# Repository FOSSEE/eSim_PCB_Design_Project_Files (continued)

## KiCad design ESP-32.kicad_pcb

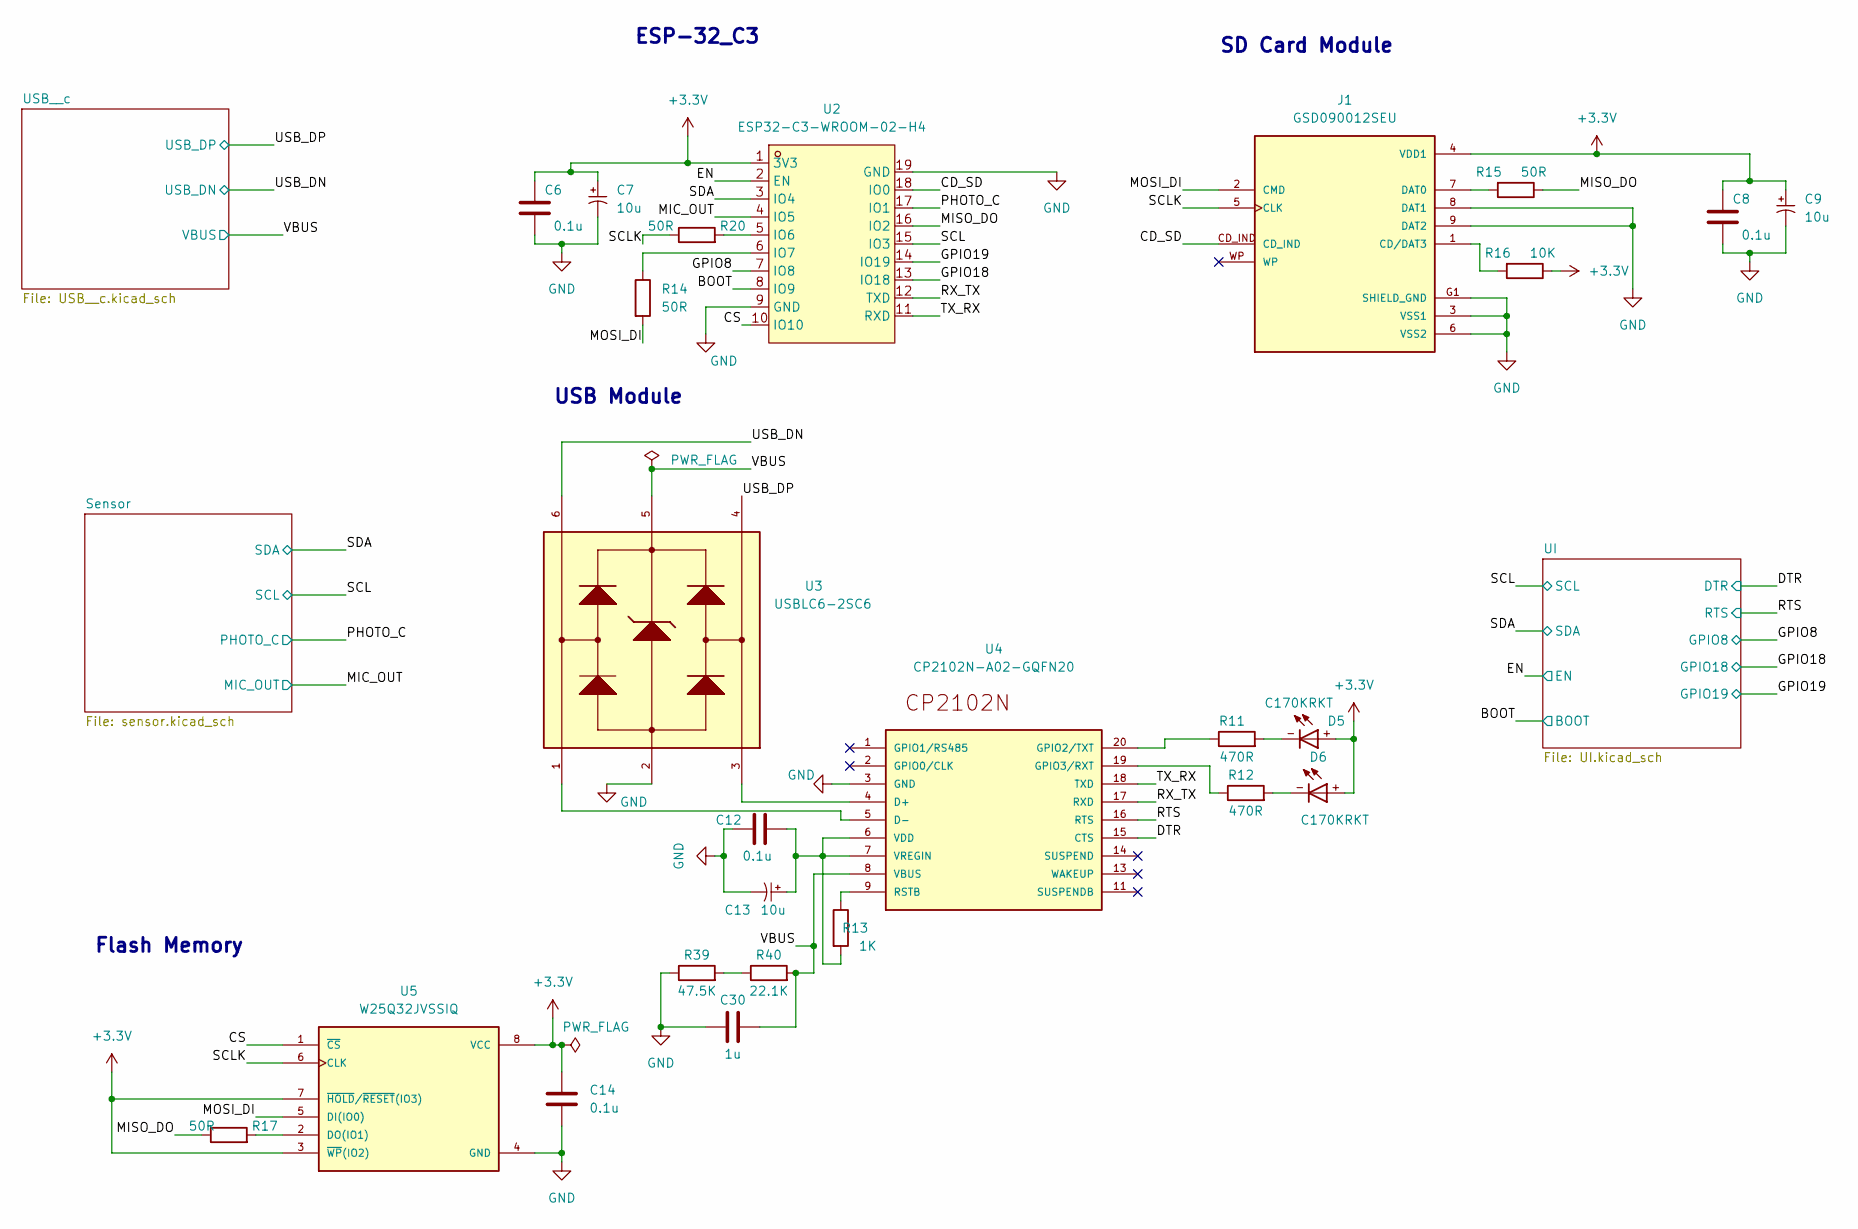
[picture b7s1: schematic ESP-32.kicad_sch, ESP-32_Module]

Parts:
C6, C8, C12, C14: 0.1u; C_0805_2012Metric
C7, C9, C13: 10u; C_0805_2012Metric
C30: 1u; C_0805_2012Metric
D5, D6: C170KRKT; DIOC200X125X110; MPN LTST-C170KRKT
J1: GSD090012SEU; AMPHENOL_GSD090012SEU; MPN GSD090012SEU
R11, R12: 470R; R_0805_2012Metric
R13: 1K; R_0805_2012Metric
R14, R15, R17, R20: 50R; R_0805_2012Metric
R16: 10K; R_0805_2012Metric
R39: 47.5K; R_0805_2012Metric
R40: 22.1K; R_0805_2012Metric
U2: ESP32-C3-WROOM-02-H4; ESP-WROOM-02; MPN ESP32-C3-WROOM-02-H4; LCSC Part C2944070
U3: USBLC6-2SC6; SOT95P280X145-6N; MPN USBLC6-2SC6
U4: CP2102N-A02-GQFN20; WFQFN-20; MPN CP2102N-A02-GQFN20
U5: W25Q32JVSSIQ; SOIC127P790X216-8N; MPN W25Q32JVSSIQ

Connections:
+3.3V: C6.1, C7.1 (A), C8.1, C9.1 (A), C14.1, D5.+, D6.+, J1.4 (VDD1), R16.1, U2.1 (3V3), U5.3 (~WP(IO2)), U5.7 (~HOLD/~RESET(IO3)), U5.8 (VCC); also elsewhere on the board
/BOOT: U2.8 (IO9); also elsewhere on the board
/CD_SD: J1.CD_IND, U2.18 (IO0)
/CS: U2.10 (IO10), U5.1 (~CS)
/DTR: U4.15 (CTS); also elsewhere on the board
/EN: U2.2 (EN); also elsewhere on the board
/GPIO8: U2.7 (IO8); also elsewhere on the board
/GPIO18: U2.13 (IO18); also elsewhere on the board
/GPIO19: U2.14 (IO19); also elsewhere on the board
/MIC_OUT: U2.4 (IO5); also elsewhere on the board
/MISO_DO: R15.1, R17.1, U2.16 (IO2)
/MOSI_DI: J1.2 (CMD), R14.2, U5.5 (DI(IO0))
/PHOTO_C: U2.17 (IO1); also elsewhere on the board
/RTS: U4.16 (RTS); also elsewhere on the board
/RX_TX: U2.12 (TXD), U4.17 (RXD)
/SCL: U2.15 (IO3); also elsewhere on the board
/SCLK: J1.5 (CLK), R20.1, U5.6 (CLK)
/SDA: U2.3 (IO4); also elsewhere on the board
/TX_RX: U2.11 (RXD), U4.18 (TXD)
/USB_DN: U3.6; also elsewhere on the board
/USB_DP: U3.4; also elsewhere on the board
/VBUS: C30.2, R40.2, U3.5, U4.8 (VBUS); also elsewhere on the board
GND: C6.2, C7.2 (B), C8.2, C9.2 (B), C12.2, C13.2 (B), C14.2, C30.1, J1.3 (VSS1), J1.6 (VSS2), J1.8 (DAT1), J1.9 (DAT2), J1.G1 (SHIELD_GND), J1.G2 (SHIELD_GND), J1.G3 (SHIELD_GND), J1.G4 (SHIELD_GND), R39.1, U2.9 (GND), U2.19 (GND), U3.2, U4.3 (GND), U4.12 (GND), U4.EXP (GND), U5.4 (GND); also elsewhere on the board
unnamed: C12.1, C13.1 (A), R13.2, U4.6 (VDD), U4.7 (VREGIN)
unnamed: D5.-, R11.2
unnamed: D6.-, R12.2
unnamed: J1.1 (CD/DAT3), R16.2
unnamed: J1.7 (DAT0), R15.2
unnamed: R11.1, U4.20 (GPIO2/TXT)
unnamed: R12.1, U4.19 (GPIO3/RXT)
unnamed: R13.1, U4.9 (RSTB)
unnamed: R14.1, U2.6 (IO7)
unnamed: R17.2, U5.2 (DO(IO1))
unnamed: R20.2, U2.5 (IO6)
unnamed: R39.2, R40.1
unnamed: U3.1, U4.5 (D-)
unnamed: U3.3, U4.4 (D+)

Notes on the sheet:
Flash Memory
SD Card Module
USB Module
ESP-32_C3

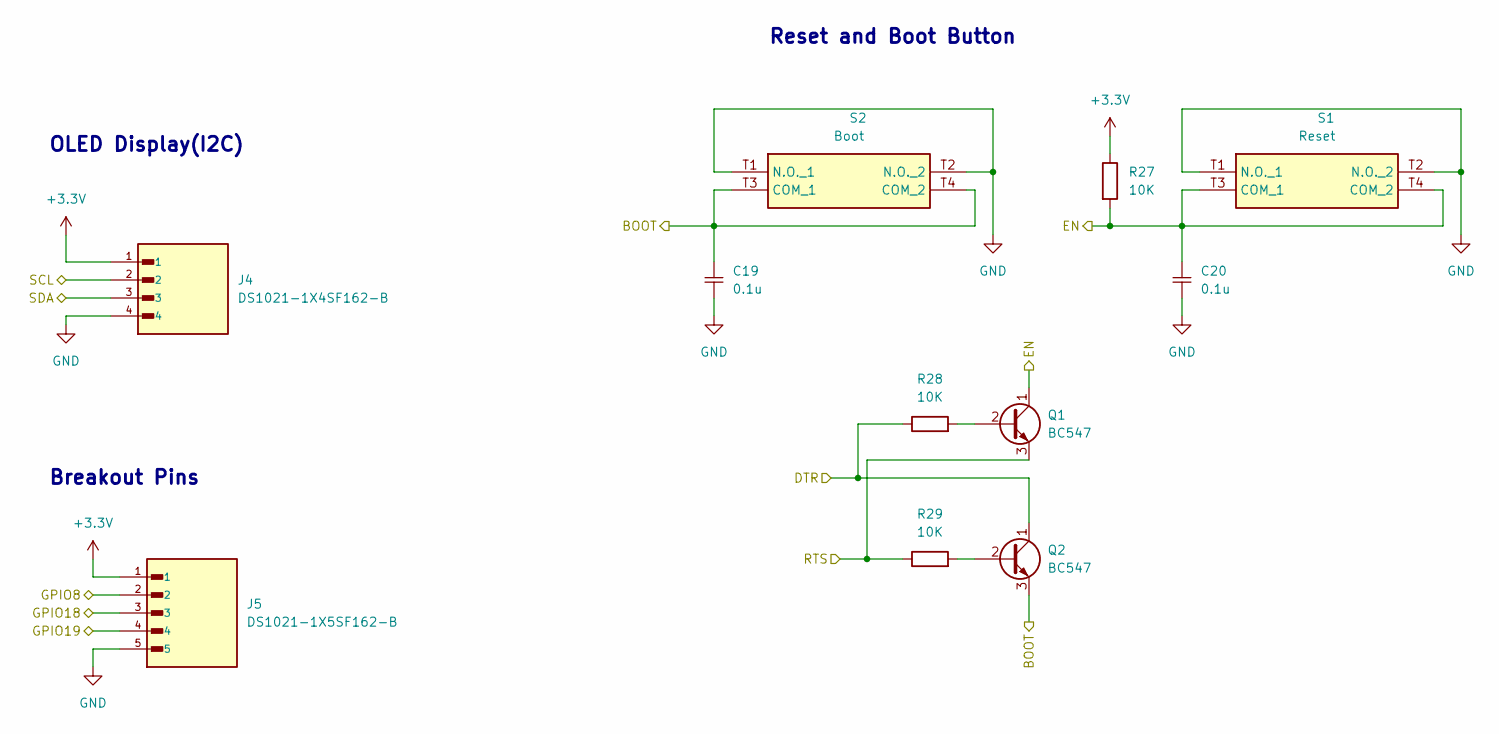
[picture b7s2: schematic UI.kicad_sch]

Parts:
C19, C20: 0.1u; C_0805_2012Metric
J4: DS1021-1X4SF162-B; PinSocket_1x04_P2.54mm_Vertical; MPN DS1021-1X4SF162-B
J5: DS1021-1X5SF162-B; PinSocket_1x05_P2.54mm_Vertical; MPN DS1021-1X5SF162-B
Q1, Q2: BC547; TO-92_Inline
R27, R28, R29: 10K; R_0805_2012Metric
S1, S2: USLPT2819DT2TR; Manufacturer_Part_Number USLPT2819DT2TR; Mouser Part Number 506-USLPT2819DT2TR

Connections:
+3.3V: J4.1, J5.1, R27.1; also elsewhere on the board
/BOOT: C19.1 (A), Q2.3 (E), S2.T3 (COM_1), S2.T4 (COM_2); also elsewhere on the board
/DTR: Q2.1 (C), R28.1; also elsewhere on the board
/EN: C20.1 (A), Q1.1 (C), R27.2, S1.T3 (COM_1), S1.T4 (COM_2); also elsewhere on the board
/GPIO8: J5.2; also elsewhere on the board
/GPIO18: J5.3; also elsewhere on the board
/GPIO19: J5.4; also elsewhere on the board
/RTS: Q1.3 (E), R29.1; also elsewhere on the board
/SCL: J4.2; also elsewhere on the board
/SDA: J4.3; also elsewhere on the board
GND: C19.2 (B), C20.2 (B), J4.4, J5.5, S1.T1 (N.O._1), S1.T2 (N.O._2), S2.T1 (N.O._1), S2.T2 (N.O._2); also elsewhere on the board
unnamed: Q1.2 (B), R28.2
unnamed: Q2.2 (B), R29.2

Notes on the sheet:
Breakout Pins
Reset and Boot Button
OLED Display(I2C)

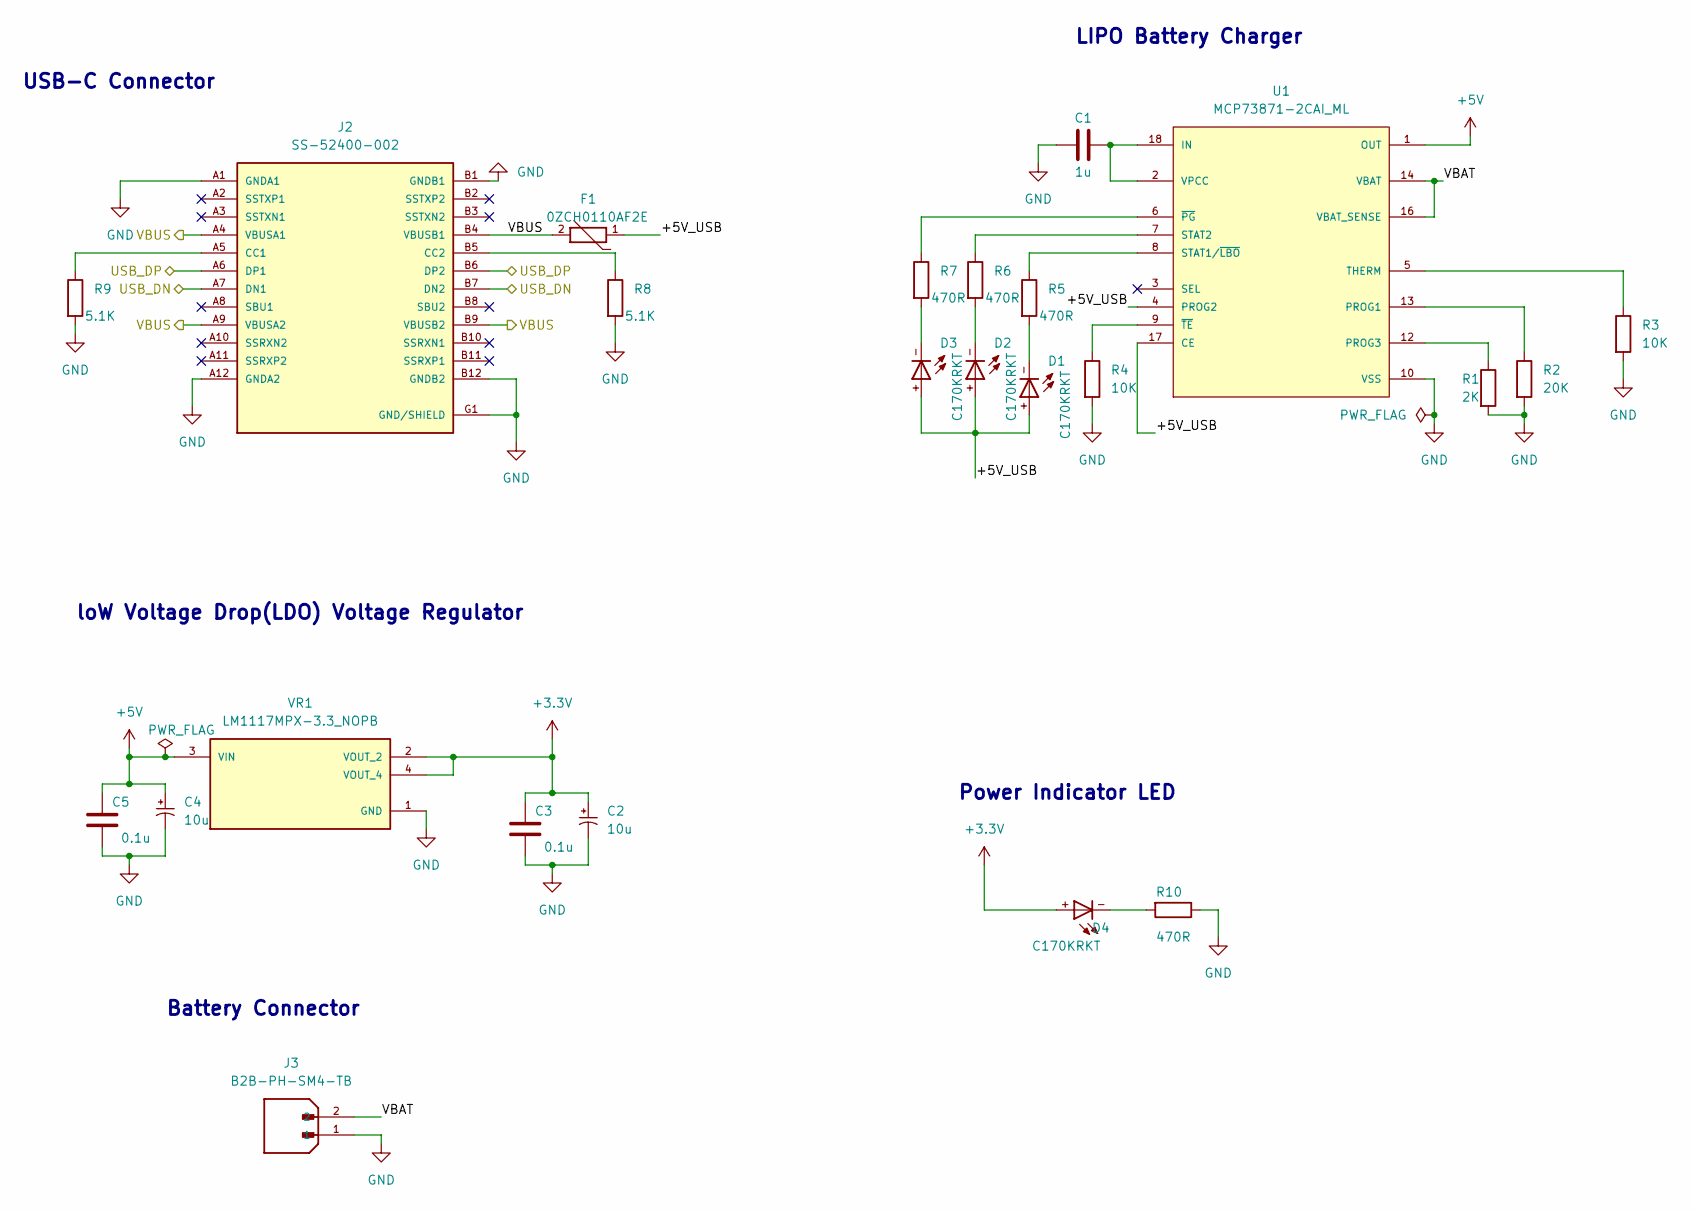
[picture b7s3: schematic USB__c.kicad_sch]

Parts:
C1: 1u; C_0805_2012Metric
C2, C4: 10u; C_0805_2012Metric
C3, C5: 0.1u; C_0805_2012Metric
D1, D2, D3, D4: C170KRKT; DIOC200X125X110; MPN LTST-C170KRKT
F1: 0ZCH0110AF2E; FUSC3225X100N; MPN 0ZCH0110AF2E
J2: SS-52400-002; BELFUSE_SS-52400-002; MPN SS-52400-002
J3: B2B-PH-SM4-TB; JST_B2B-PH-SM4-TB; MPN B2B-PH-SM4-TB
R1: 2K; R_0805_2012Metric
R2: 20K; R_0805_2012Metric
R3, R4: 10K; R_0805_2012Metric
R5, R6, R7, R10: 470R; R_0805_2012Metric
R8, R9: 5.1K; R_0805_2012Metric
U1: MCP73871-2CAI_ML; QFN50P400X400X100-21N; MPN MCP73871-2CAI/ML
VR1: LM1117MPX-3.3_NOPB; VREG_LM1117MPX-3.3_NOPB; MPN LM1117MPX-3.3/NOPB

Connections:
+3.3V: C2.1 (A), C3.1, D4.+, VR1.2 (VOUT_2), VR1.4 (VOUT_4); also elsewhere on the board
+5V: C4.1 (A), C5.1, U1.1 (OUT), U1.20 (OUT), VR1.3 (VIN)
/USB_DN: J2.A7 (DN1), J2.B7 (DN2); also elsewhere on the board
/USB_DP: J2.A6 (DP1), J2.B6 (DP2); also elsewhere on the board
/USB__c/+5V_USB: D1.+, D2.+, D3.+, F1.1, U1.4 (PROG2), U1.17 (CE)
/USB__c/VBAT: J3.2, U1.14 (VBAT), U1.15 (VBAT), U1.16 (VBAT_SENSE)
/VBUS: F1.2, J2.A4 (VBUSA1), J2.A9 (VBUSA2), J2.B4 (VBUSB1), J2.B9 (VBUSB2); also elsewhere on the board
GND: C1.2, C2.2 (B), C3.2, C4.2 (B), C5.2, J2.A1 (GNDA1), J2.A12 (GNDA2), J2.B1 (GNDB1), J2.B12 (GNDB2), J2.G1 (GND/SHIELD), J2.G2 (GND/SHIELD), J2.G3 (GND/SHIELD), J2.G4 (GND/SHIELD), J2.S1 (GND/SHIELD), J2.S2 (GND/SHIELD), J2.S3 (GND/SHIELD), J2.S4 (GND/SHIELD), J3.1, R1.2, R2.2, R3.2, R4.2, R8.2, R9.2, R10.1, U1.10 (VSS), U1.11 (VSS), U1.21 (VSS), VR1.1 (GND); also elsewhere on the board
unnamed: C1.1, U1.2 (VPCC), U1.18 (IN), U1.19 (IN)
unnamed: D1.-, R5.2
unnamed: D2.-, R6.2
unnamed: D3.-, R7.2
unnamed: D4.-, R10.2
unnamed: J2.A5 (CC1), R9.1
unnamed: J2.B5 (CC2), R8.1
unnamed: R1.1, U1.12 (PROG3)
unnamed: R2.1, U1.13 (PROG1)
unnamed: R3.1, U1.5 (THERM)
unnamed: R4.1, U1.9 (~TE)
unnamed: R5.1, U1.8 (STAT1/~LBO)
unnamed: R6.1, U1.7 (STAT2)
unnamed: R7.1, U1.6 (~PG)

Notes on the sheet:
USB-C Connector
LIPO Battery Charger
Power Indicator LED
Battery Connector
loW Voltage Drop(LDO) Voltage Regulator

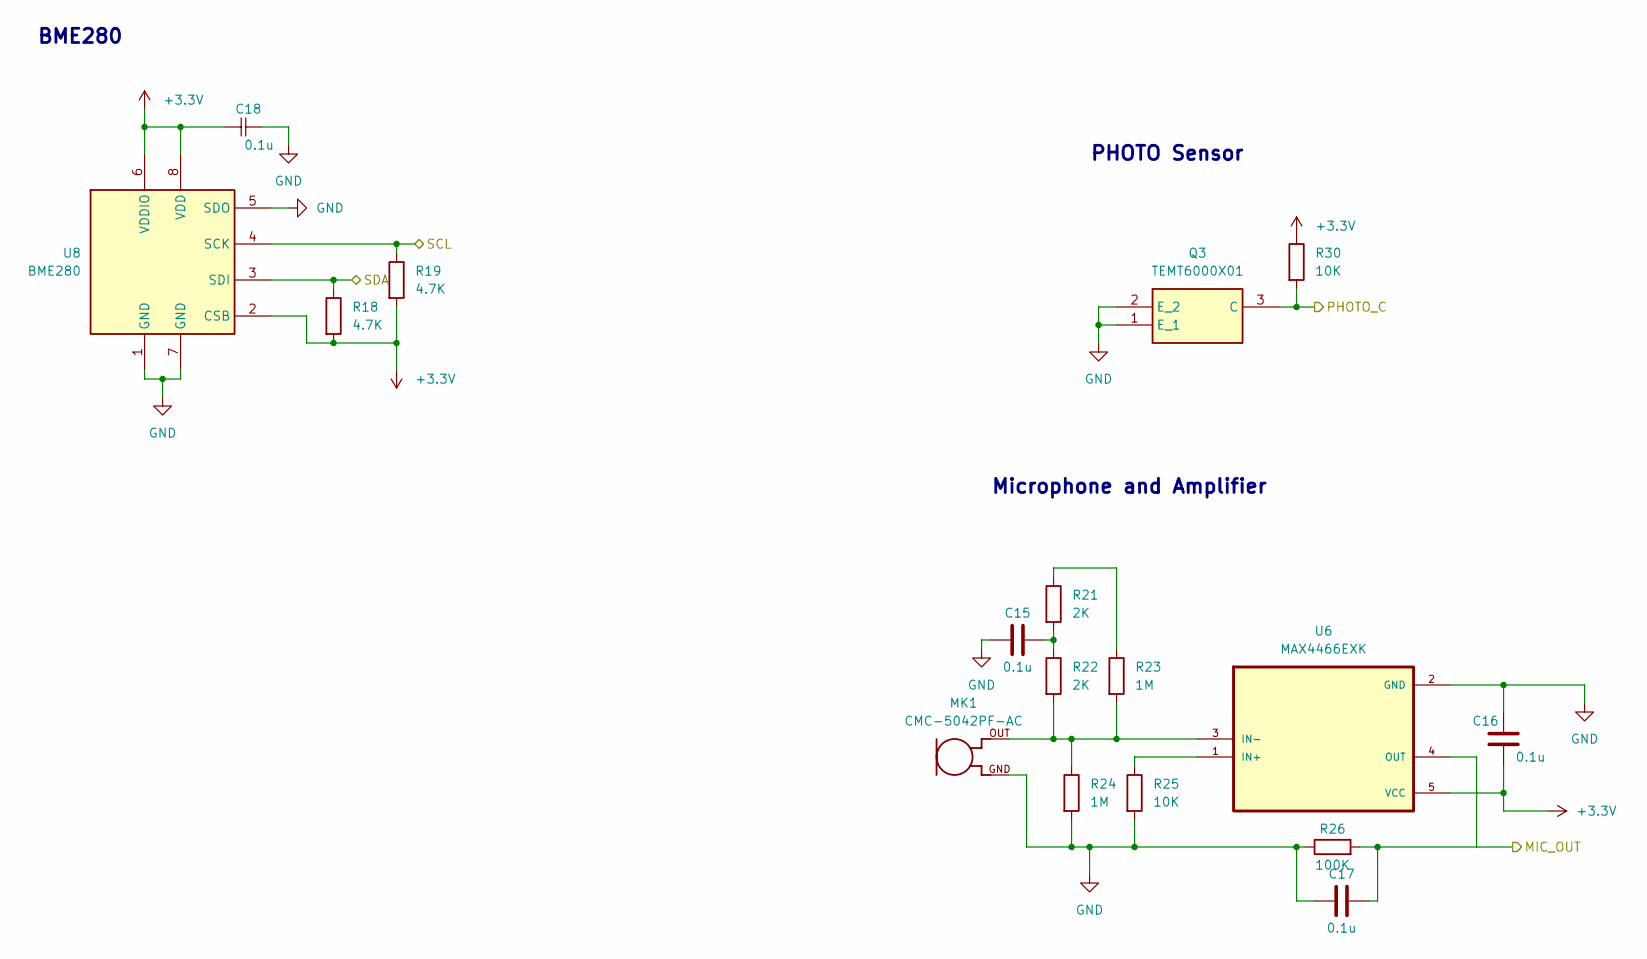
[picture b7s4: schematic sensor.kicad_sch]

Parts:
C15, C16, C17, C18: 0.1u; C_0805_2012Metric
MK1: CMC-5042PF-AC; CUI_CMC-5042PF-AC; MPN CMC-5042PF-AC
Q3: TEMT6000X01; Manufacturer_Part_Number TEMT6000X01; Mouser Part Number 78-TEMT6000
R18, R19: 4.7K; R_0805_2012Metric
R21, R22: 2K; R_0805_2012Metric
R23, R24: 1M; R_0805_2012Metric
R25, R30: 10K; R_0805_2012Metric
R26: 100K; R_0805_2012Metric
U6: MAX4466EXK; SOT65P210X110-5N; MPN MAX4466EXK+T
U8: BME280; Bosch_LGA-8_2.5x2.5mm_P0.65mm_ClockwisePinNumbering

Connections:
+3.3V: C16.2, C18.1 (A), R18.2, R19.2, R30.1, U6.5 (VCC), U8.2 (CSB), U8.6 (VDDIO), U8.8 (VDD); also elsewhere on the board
/MIC_OUT: C17.1, R26.2, U6.4 (OUT); also elsewhere on the board
/PHOTO_C: Q3.3 (C), R30.2; also elsewhere on the board
/SCL: R19.1, U8.4 (SCK); also elsewhere on the board
/SDA: R18.1, U8.3 (SDI); also elsewhere on the board
GND: C15.2, C16.1, C17.2, C18.2 (B), MK1.GND, Q3.1 (E_1), Q3.2 (E_2), R24.2, R25.2, R26.1, U6.2 (GND), U8.1 (GND), U8.5 (SDO), U8.7 (GND); also elsewhere on the board
unnamed: C15.1, R21.2, R22.1
unnamed: MK1.OUT, R22.2, R23.2, R24.1, U6.3 (IN-)
unnamed: R21.1, R23.1
unnamed: R25.1, U6.1 (IN+)

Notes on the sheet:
Microphone and Amplifier
PHOTO Sensor
BME280

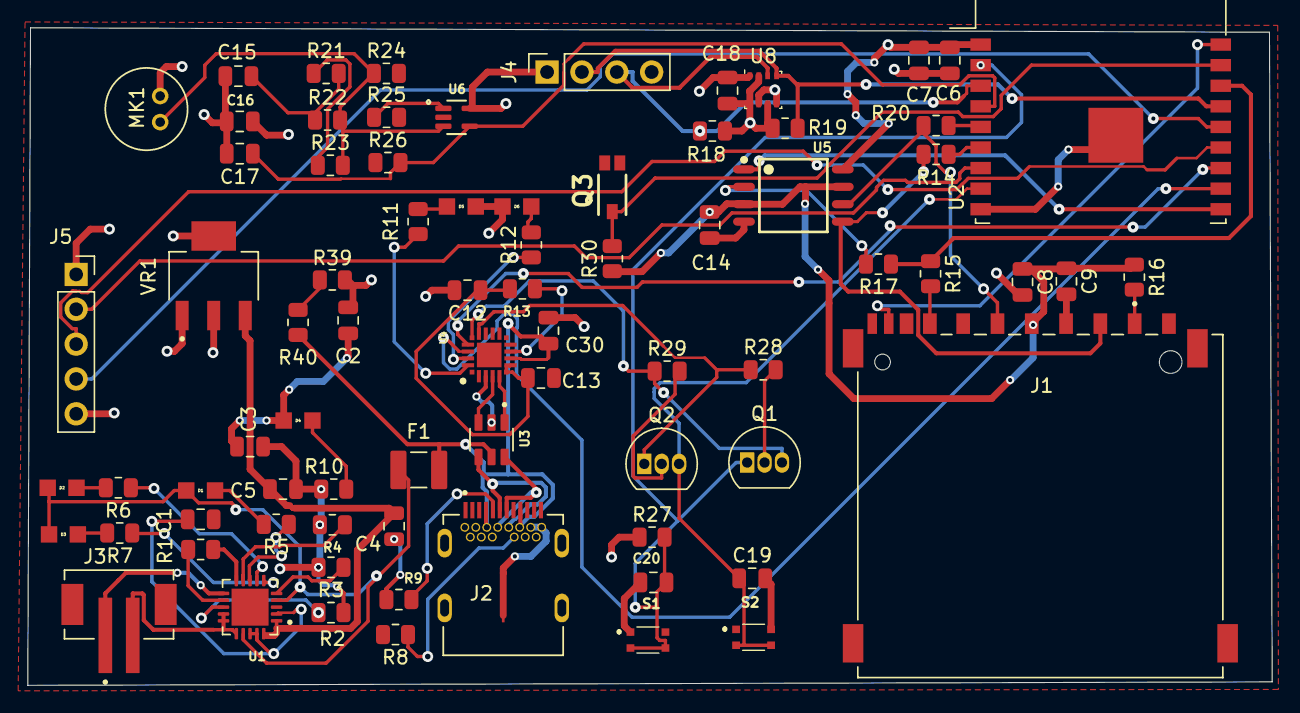
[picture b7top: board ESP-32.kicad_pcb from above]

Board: 4 copper layers, 90.7 x 47.9 mm, 77 parts (0 on the bottom side), 60 nets.

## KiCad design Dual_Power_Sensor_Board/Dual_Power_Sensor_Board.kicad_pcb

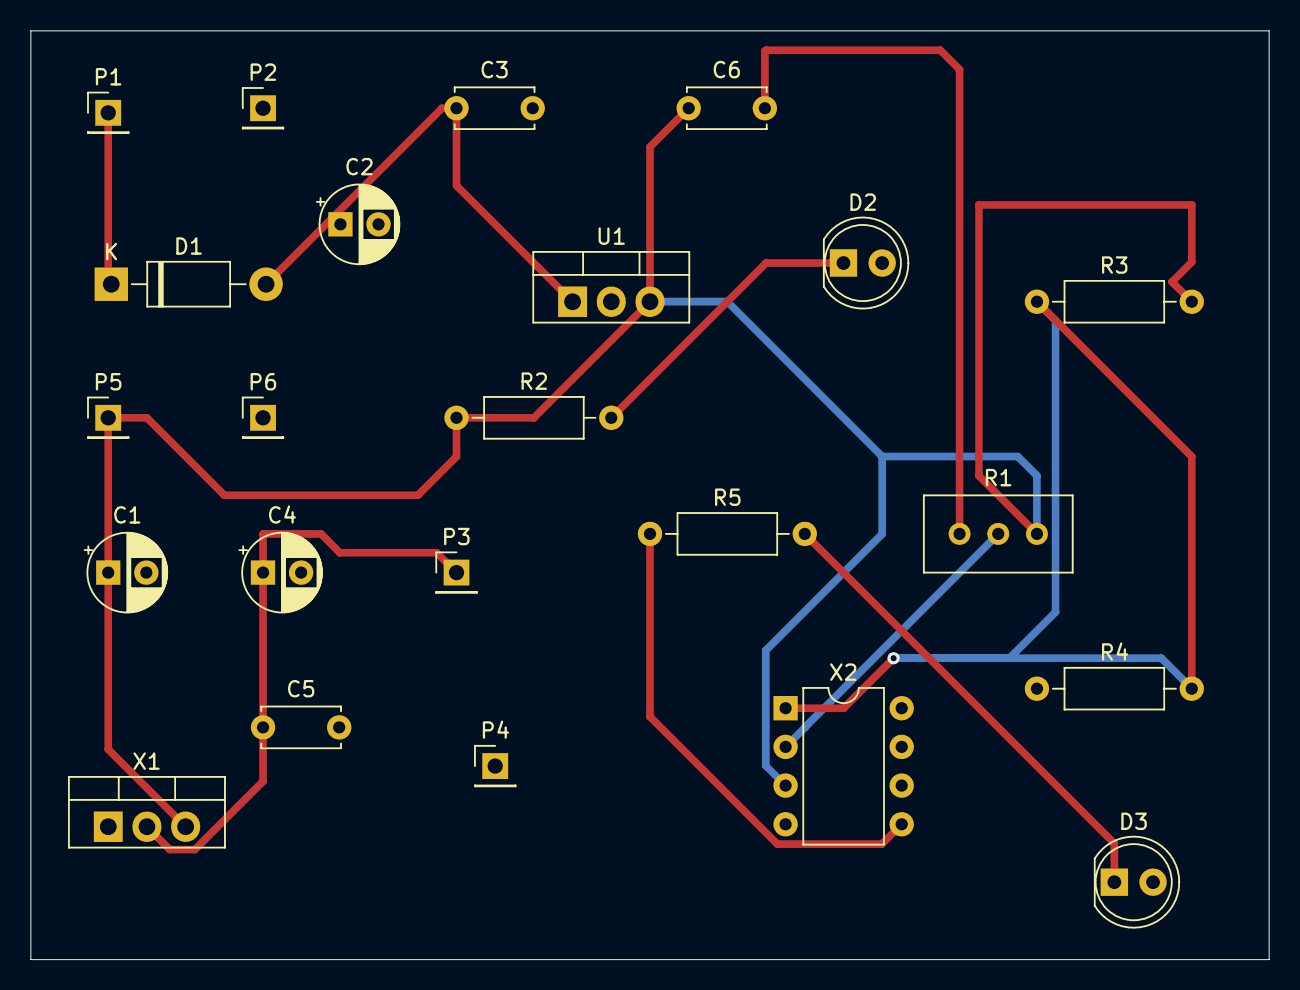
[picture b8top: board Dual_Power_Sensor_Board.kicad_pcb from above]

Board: 2 copper layers, 81.3 x 61.0 mm, 23 parts (0 on the bottom side), 10 nets.

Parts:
C1, C2, C4: 10uF; CP_Radial_D5.0mm_P2.50mm
C3, C5, C6: 100nF; C_Disc_D5.0mm_W2.5mm_P5.00mm
D1: eSim_Diode; D_DO-41_SOD81_P10.16mm_Horizontal
D2, D3: eSim_LED; LED_D5.0mm
P1: CONN_12V_IN; PinHeader_1x01_P2.54mm_Vertical
P2, P6: CONNECTOR_PSPICE; PinHeader_1x01_P2.54mm_Vertical
P3: CONN_3V3_out; PinHeader_1x01_P2.54mm_Vertical
P4: CONN_GND_3V3; PinHeader_1x01_P2.54mm_Vertical
P5: CONN_5V_out; PinHeader_1x01_P2.54mm_Vertical
R1: POT_10k; Potentiometer_Bourns_3296W_Vertical
R2, R5: 330; R_Axial_DIN0207_L6.3mm_D2.5mm_P10.16mm_Horizontal
R3: Sensor_10k; R_Axial_DIN0207_L6.3mm_D2.5mm_P10.16mm_Horizontal
R4: 10k; R_Axial_DIN0207_L6.3mm_D2.5mm_P10.16mm_Horizontal
U1: LM7805C_PSPICE; TO-220-3_Vertical
X1: LT1117-3.3; TO-220-3_Vertical
X2: LT1001; DIP-8_W7.62mm

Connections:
GND: C1.2, C2.2, C3.2, C4.2, C5.2, C6.2, D2.2 (K), D3.2 (K), P2.1, P4.1, P6.1, R1.3, R4.1, U1.2, X1.1 (GND), X2.4 (V-)
unnamed: C1.1, C6.1, P5.1, R1.1, R2.1, R3.2, U1.3, X1.3 (IN), X2.3 (V+)
unnamed: C2.1, C3.1, D1.2 (K), U1.1
unnamed: C4.1, C5.1, P3.1, X1.2 (OUT)
unnamed: D1.1 (A), P1.1
unnamed: D2.1 (A), R2.2
unnamed: D3.1 (A), R5.2
unnamed: R1.2, X2.2 (In-)
unnamed: R3.1, R4.2, X2.1 (In+)
unnamed: R5.1, X2.5 (OUT)
